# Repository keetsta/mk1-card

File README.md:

# mk1-card

hardware for mk-1, a pcb business card: an RP2350 with a 16 × 9 LED matrix, a light sensor, one button and USB-C. this repository holds the schematic, the board, the fabrication files and the scripts that generate them. the firmware lives in a separate repository.

## board

- 85.6 × 54 mm (bank card size), 4 layers, 1.0 mm, ENIG, white mask, black silkscreen
- RP2350A with the crystal and 16 MB flash of the Raspberry Pi minimal design R4. the core runs from a 1.1 V LDO instead of the on-chip switching regulator
- IS31FL3731 driving 144 red 0603 LEDs from VBUS
- TEMT6200 light sensor on ADC0 with a switchable load, AT24C02 EEPROM, USB-C with ESD protection, SWD pads on the back
- one button, wired as BOOTSEL: hold it while plugging in the cable to get the UF2 drive
- every chip sits on the back, so assembly is double-sided

pins and parts: `tools/design.py`. BOM with prices (in Russian): `bom.md`.

## build

the KiCad files are generated: change `tools/design.py` or the scripts in `tools/`, never the board or the schematic by hand. the scripts expect Windows with KiCad 9 in `C:\Program Files\KiCad\9.0` and Python 3 with `fontTools` and `openpyxl`.

```
python tools/make_fplib.py
python tools/gen_sch.py
python tools/make_text.py "tools/fonts/InterTight[wght].ttf"
"C:\Program Files\KiCad\9.0\bin\python.exe" tools/build_pcb.py
python tools/make_fab.py
python tools/make_bom.py
```

`build_pcb.py` places, routes and pours the board in about a minute. the build is deterministic: the same input gives the same board byte for byte. ERC (`kicad-cli sch erc`) and DRC (`kicad-cli pcb drc --schematic-parity`) both report 0 errors.

## ordering

JLCPCB: upload `fab/card-gerbers.zip`, `fab/card-bom.csv` and `fab/card-cpl.csv`. parts go on both sides, which means Standard PCBA with 5 mm rails on the long edges: snap them off and sand the edge. turn on parts placement confirmation and check the LED cathodes, the light sensor and pin 1 of U1..U8 in the preview.

`fab/card-cpl.csv` is written in JLC's footprint orientations. any other assembler gets `fab/card-cpl-kicad.csv` and the assembly drawings `fab/card-assembly-top.pdf` and `fab/card-assembly-bottom.pdf`.

## license

MIT, see `LICENSE`. the RP2350 core is adapted from the Raspberry Pi RP2350A minimal design (MIT, `tools/ref/LICENSE-RPi-minimal.txt`). Inter Tight is under the SIL Open Font License (`tools/fonts/OFL-InterTight.txt`).

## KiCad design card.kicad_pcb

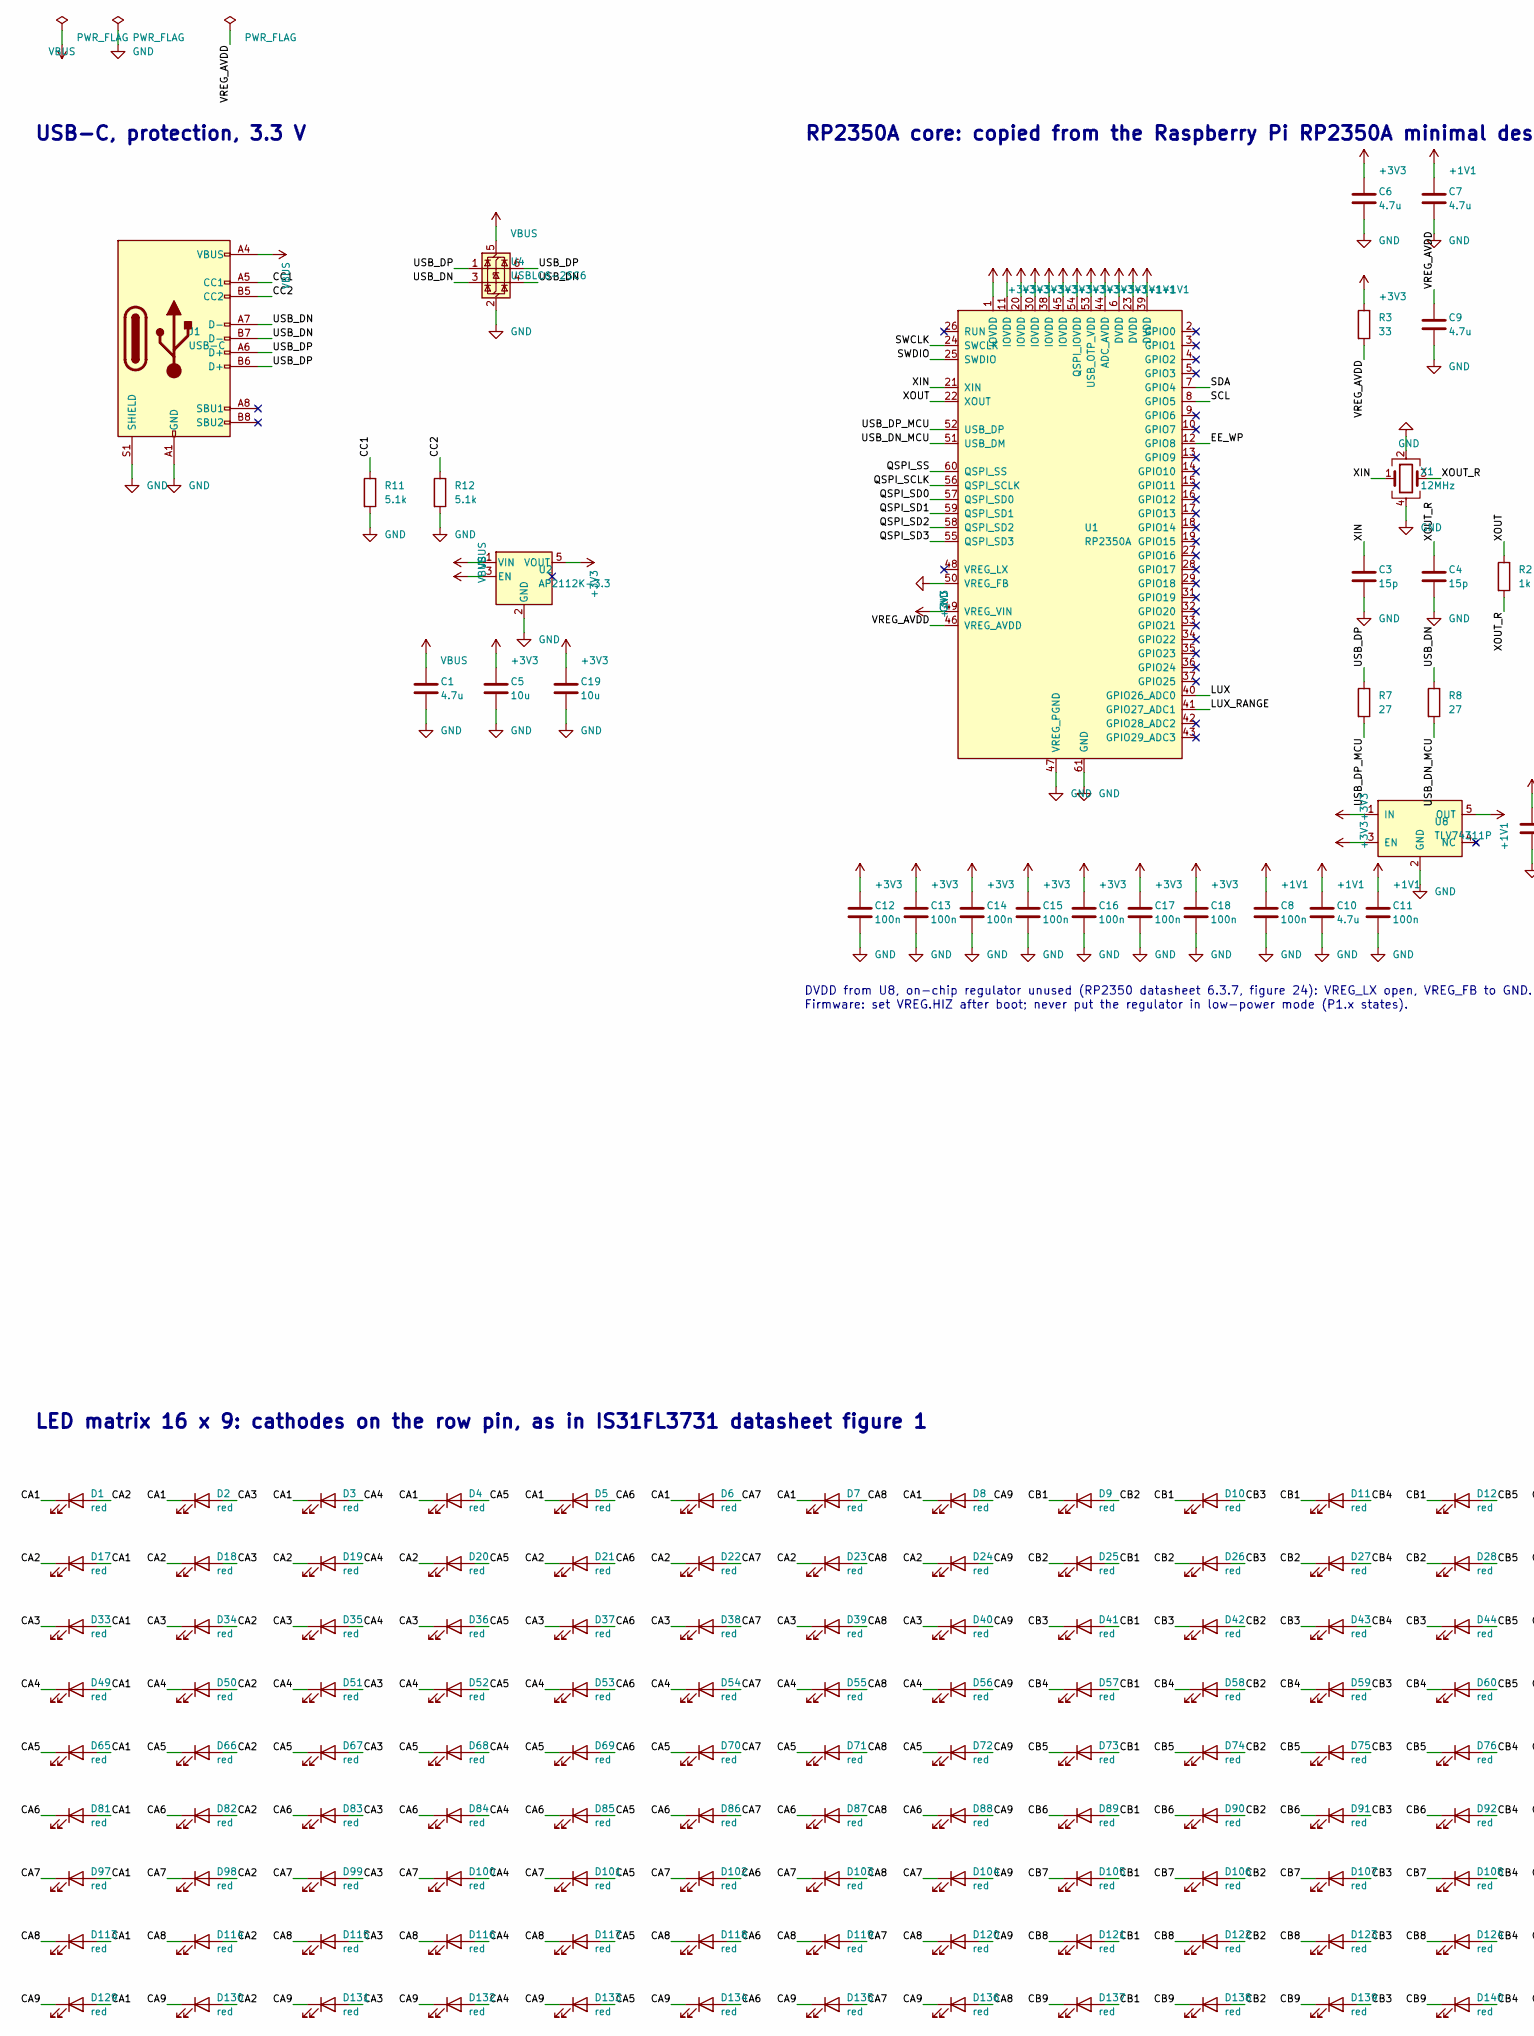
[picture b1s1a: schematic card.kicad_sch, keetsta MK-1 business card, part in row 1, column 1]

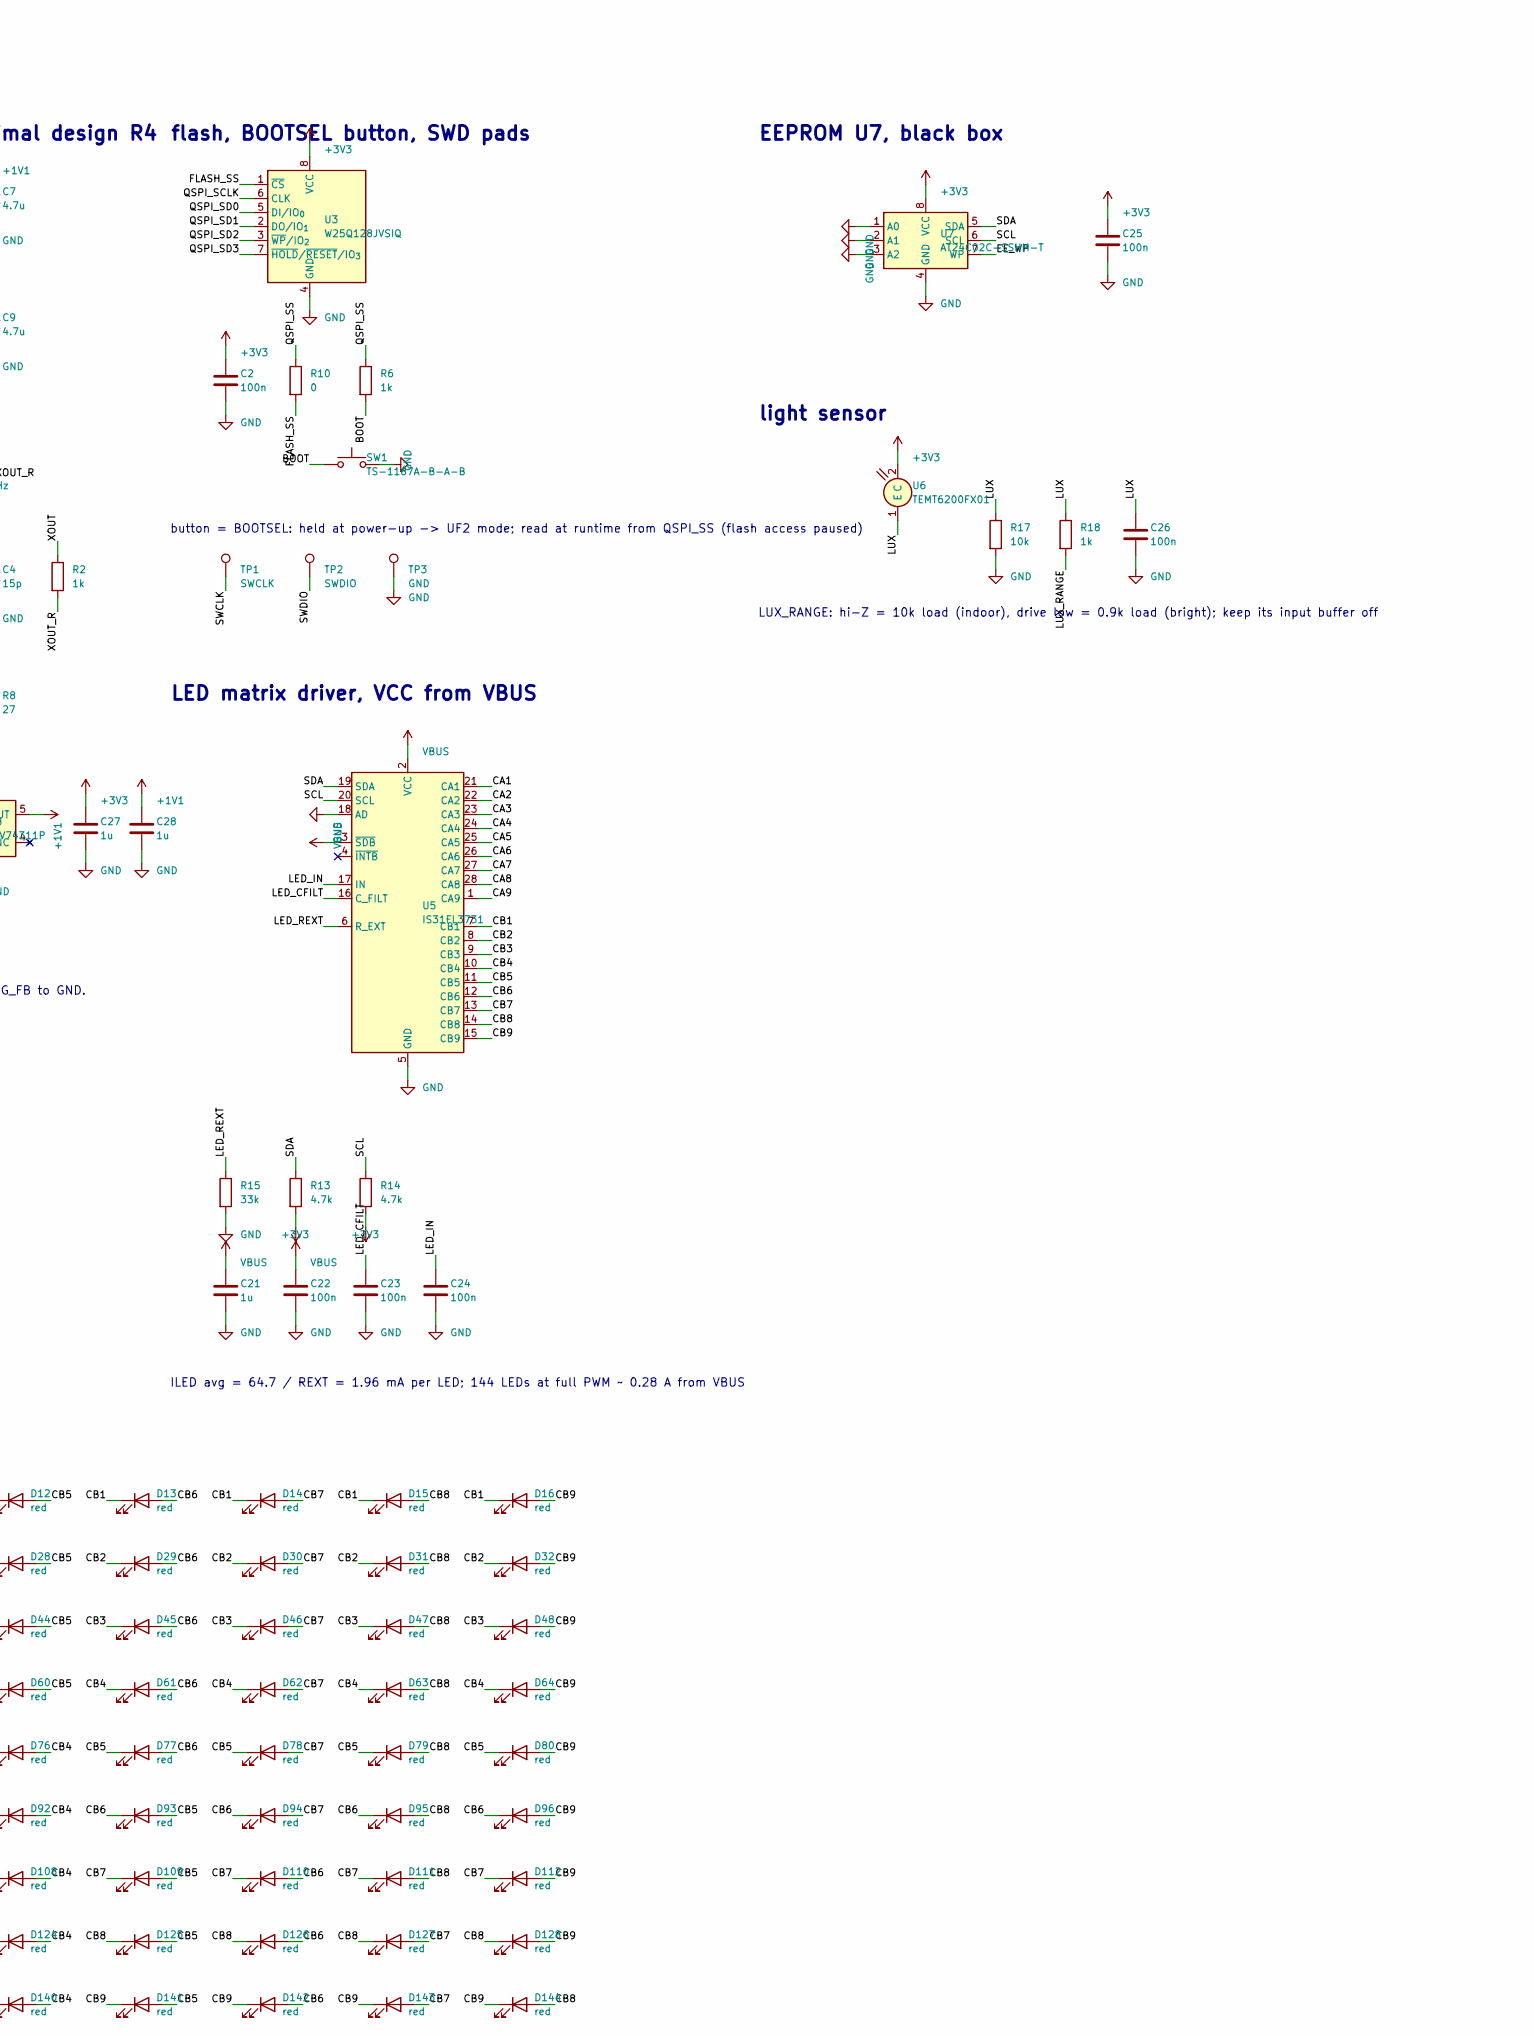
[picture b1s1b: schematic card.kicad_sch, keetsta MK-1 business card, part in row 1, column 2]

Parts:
C1: 4.7u; C_0603_1608Metric; LCSC C19666
C2, C8, C11, C12, C13, C14, C15, C16, C17, C18: 100n; RPi_capc1005x50; LCSC C1525
C3, C4: 15p; RPi_capc1005x50; LCSC C1548
C5, C19: 10u; C_0805_2012Metric; LCSC C15850
C6, C7: 4.7u; RPi_capc1005x50_wide; LCSC C23733
C9, C10: 4.7u; RPi_capc1005x50; LCSC C23733
C21, C27, C28: 1u; C_0402_1005Metric; LCSC C52923
C22, C23, C24, C25, C26: 100n; C_0402_1005Metric; LCSC C1525
D1, D2, D3, D4, D5, D6, D7, D8, D9, D10, D11, D12, D13, D14, D15, D16, D17, D18, D19, D20, D21, D22, D23, D24, D25, D26, D27, D28, D29, D30, D31, D32, D33, D34, D35, D36, D37, D38, D39, D40, D41, D42, D43, D44, D45, D46, D47, D48, D49, D50, D51, D52, D53, D54, D55, D56, D57, D58, D59, D60, D61, D62, D63, D64, D65, D66, D67, D68, D69, D70, D71, D72, D73, D74, D75, D76, D77, D78, D79, D80, D81, D82, D83, D84, D85, D86, D87, D88, D89, D90, D91, D92, D93, D94, D95, D96, D97, D98, D99, D100, D101, D102, D103, D104, D105, D106, D107, D108, D109, D110, D111, D112, D113, D114, D115, D116, D117, D118, D119, D120, D121, D122, D123, D124, D125, D126, D127, D128, D129, D130, D131, D132, D133, D134, D135, D136, D137, D138, D139, D140, D141, D142, D143, D144: red; LED_0603_KT; LCSC C2286
J1: USB-C; USB_C_Receptacle_HRO_TYPE-C-31-M-12; LCSC C165948
R2, R6: 1k; RPi_resc1005x35; LCSC C11702
R3: 33; RPi_resc1005x35; LCSC C25105
R7, R8: 27; RPi_resc1005x35; LCSC C25100
R10: 0; RPi_resc1005x35; LCSC C17168
R11, R12: 5.1k; R_0402_1005Metric; LCSC C25905
R13, R14: 4.7k; R_0402_1005Metric; LCSC C25900
R15: 33k; R_0402_1005Metric; LCSC C25779
R17: 10k; R_0402_1005Metric; LCSC C25744
R18: 1k; R_0402_1005Metric; LCSC C11702
SW1: TS-1187A-B-A-B; SW_Push_1P1T_XKB_TS-1187A; LCSC C318884
TP1: SWCLK; TestPoint_Pad_D1.0mm
TP2: SWDIO; TestPoint_Pad_D1.0mm
TP3: GND; TestPoint_Pad_D1.0mm
U1: RP2350A; RPi_rp2350a_vias; LCSC C42411118
U2: AP2112K-3.3; SOT-23-5; LCSC C51118
U3: W25Q128JVSIQ; RPi_soic127p790x195-8; LCSC C97521
U4: USBLC6-2SC6; SOT-23-6; LCSC C7519
U5: IS31FL3731; QFN-28-1EP_4x4mm_P0.4mm_EP2.4x2.4mm_ThermalVias; LCSC C191206
U6: TEMT6200FX01; LCSC C143695
U7: AT24C02C-SSHM-T; SOIC-8_3.9x4.9mm_P1.27mm; LCSC C6203
U8: TLV74311P; SOT-23-5; LCSC C485147
X1: 12MHz; RPi_xtalcc320x250x80-4; LCSC C20625731

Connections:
+1V1: C7.1, C8.1, C10.1, C11.1, C28.1, U1.6 (DVDD), U1.23 (DVDD), U1.39 (DVDD), U8.5 (OUT)
+3V3: C2.1, C5.1, C6.1, C12.1, C13.1, C14.1, C15.1, C16.1, C17.1, C18.1, C19.1, C25.1, C27.1, R3.1, R13.2, R14.2, U1.1 (IOVDD), U1.11 (IOVDD), U1.20 (IOVDD), U1.30 (IOVDD), U1.38 (IOVDD), U1.44 (ADC_AVDD), U1.45 (IOVDD), U1.49 (VREG_VIN), U1.53 (USB_OTP_VDD), U1.54 (QSPI_IOVDD), U2.5 (VOUT), U3.8 (VCC), U6.2 (C), U7.8 (VCC), U8.1 (IN), U8.3 (EN)
/BOOT: R6.2, SW1.1
/CA1: D1.1 (K), D2.1 (K), D3.1 (K), D4.1 (K), D5.1 (K), D6.1 (K), D7.1 (K), D8.1 (K), D17.2 (A), D33.2 (A), D49.2 (A), D65.2 (A), D81.2 (A), D97.2 (A), D113.2 (A), D129.2 (A), U5.21 (CA1)
/CA2: D1.2 (A), D17.1 (K), D18.1 (K), D19.1 (K), D20.1 (K), D21.1 (K), D22.1 (K), D23.1 (K), D24.1 (K), D34.2 (A), D50.2 (A), D66.2 (A), D82.2 (A), D98.2 (A), D114.2 (A), D130.2 (A), U5.22 (CA2)
/CA3: D2.2 (A), D18.2 (A), D33.1 (K), D34.1 (K), D35.1 (K), D36.1 (K), D37.1 (K), D38.1 (K), D39.1 (K), D40.1 (K), D51.2 (A), D67.2 (A), D83.2 (A), D99.2 (A), D115.2 (A), D131.2 (A), U5.23 (CA3)
/CA4: D3.2 (A), D19.2 (A), D35.2 (A), D49.1 (K), D50.1 (K), D51.1 (K), D52.1 (K), D53.1 (K), D54.1 (K), D55.1 (K), D56.1 (K), D68.2 (A), D84.2 (A), D100.2 (A), D116.2 (A), D132.2 (A), U5.24 (CA4)
/CA5: D4.2 (A), D20.2 (A), D36.2 (A), D52.2 (A), D65.1 (K), D66.1 (K), D67.1 (K), D68.1 (K), D69.1 (K), D70.1 (K), D71.1 (K), D72.1 (K), D85.2 (A), D101.2 (A), D117.2 (A), D133.2 (A), U5.25 (CA5)
/CA6: D5.2 (A), D21.2 (A), D37.2 (A), D53.2 (A), D69.2 (A), D81.1 (K), D82.1 (K), D83.1 (K), D84.1 (K), D85.1 (K), D86.1 (K), D87.1 (K), D88.1 (K), D102.2 (A), D118.2 (A), D134.2 (A), U5.26 (CA6)
/CA7: D6.2 (A), D22.2 (A), D38.2 (A), D54.2 (A), D70.2 (A), D86.2 (A), D97.1 (K), D98.1 (K), D99.1 (K), D100.1 (K), D101.1 (K), D102.1 (K), D103.1 (K), D104.1 (K), D119.2 (A), D135.2 (A), U5.27 (CA7)
/CA8: D7.2 (A), D23.2 (A), D39.2 (A), D55.2 (A), D71.2 (A), D87.2 (A), D103.2 (A), D113.1 (K), D114.1 (K), D115.1 (K), D116.1 (K), D117.1 (K), D118.1 (K), D119.1 (K), D120.1 (K), D136.2 (A), U5.28 (CA8)
/CA9: D8.2 (A), D24.2 (A), D40.2 (A), D56.2 (A), D72.2 (A), D88.2 (A), D104.2 (A), D120.2 (A), D129.1 (K), D130.1 (K), D131.1 (K), D132.1 (K), D133.1 (K), D134.1 (K), D135.1 (K), D136.1 (K), U5.1 (CA9)
/CB1: D9.1 (K), D10.1 (K), D11.1 (K), D12.1 (K), D13.1 (K), D14.1 (K), D15.1 (K), D16.1 (K), D25.2 (A), D41.2 (A), D57.2 (A), D73.2 (A), D89.2 (A), D105.2 (A), D121.2 (A), D137.2 (A), U5.7 (CB1)
/CB2: D9.2 (A), D25.1 (K), D26.1 (K), D27.1 (K), D28.1 (K), D29.1 (K), D30.1 (K), D31.1 (K), D32.1 (K), D42.2 (A), D58.2 (A), D74.2 (A), D90.2 (A), D106.2 (A), D122.2 (A), D138.2 (A), U5.8 (CB2)
/CB3: D10.2 (A), D26.2 (A), D41.1 (K), D42.1 (K), D43.1 (K), D44.1 (K), D45.1 (K), D46.1 (K), D47.1 (K), D48.1 (K), D59.2 (A), D75.2 (A), D91.2 (A), D107.2 (A), D123.2 (A), D139.2 (A), U5.9 (CB3)
/CB4: D11.2 (A), D27.2 (A), D43.2 (A), D57.1 (K), D58.1 (K), D59.1 (K), D60.1 (K), D61.1 (K), D62.1 (K), D63.1 (K), D64.1 (K), D76.2 (A), D92.2 (A), D108.2 (A), D124.2 (A), D140.2 (A), U5.10 (CB4)
/CB5: D12.2 (A), D28.2 (A), D44.2 (A), D60.2 (A), D73.1 (K), D74.1 (K), D75.1 (K), D76.1 (K), D77.1 (K), D78.1 (K), D79.1 (K), D80.1 (K), D93.2 (A), D109.2 (A), D125.2 (A), D141.2 (A), U5.11 (CB5)
/CB6: D13.2 (A), D29.2 (A), D45.2 (A), D61.2 (A), D77.2 (A), D89.1 (K), D90.1 (K), D91.1 (K), D92.1 (K), D93.1 (K), D94.1 (K), D95.1 (K), D96.1 (K), D110.2 (A), D126.2 (A), D142.2 (A), U5.12 (CB6)
/CB7: D14.2 (A), D30.2 (A), D46.2 (A), D62.2 (A), D78.2 (A), D94.2 (A), D105.1 (K), D106.1 (K), D107.1 (K), D108.1 (K), D109.1 (K), D110.1 (K), D111.1 (K), D112.1 (K), D127.2 (A), D143.2 (A), U5.13 (CB7)
/CB8: D15.2 (A), D31.2 (A), D47.2 (A), D63.2 (A), D79.2 (A), D95.2 (A), D111.2 (A), D121.1 (K), D122.1 (K), D123.1 (K), D124.1 (K), D125.1 (K), D126.1 (K), D127.1 (K), D128.1 (K), D144.2 (A), U5.14 (CB8)
/CB9: D16.2 (A), D32.2 (A), D48.2 (A), D64.2 (A), D80.2 (A), D96.2 (A), D112.2 (A), D128.2 (A), D137.1 (K), D138.1 (K), D139.1 (K), D140.1 (K), D141.1 (K), D142.1 (K), D143.1 (K), D144.1 (K), U5.15 (CB9)
/CC1: J1.A5 (CC1), R11.1
/CC2: J1.B5 (CC2), R12.1
/EE_WP: U1.12 (GPIO8), U7.7 (WP)
/FLASH_SS: R10.2, U3.1 (~CS)
/LED_CFILT: C23.1, U5.16 (C_FILT)
/LED_IN: C24.1, U5.17 (IN)
/LED_REXT: R15.1, U5.6 (R_EXT)
/LUX: C26.1, R17.1, R18.1, U1.40 (GPIO26_ADC0), U6.1 (E)
/LUX_RANGE: R18.2, U1.41 (GPIO27_ADC1)
/QSPI_SCLK: U1.56 (QSPI_SCLK), U3.6 (CLK)
/QSPI_SD0: U1.57 (QSPI_SD0), U3.5 (DI/IO_{0})
/QSPI_SD1: U1.59 (QSPI_SD1), U3.2 (DO/IO_{1})
/QSPI_SD2: U1.58 (QSPI_SD2), U3.3 (~WP/IO_{2})
/QSPI_SD3: U1.55 (QSPI_SD3), U3.7 (~HOLD/~RESET/IO_{3})
/QSPI_SS: R6.1, R10.1, U1.60 (QSPI_SS)
/SCL: R14.1, U1.8 (GPIO5), U5.20 (SCL), U7.6 (SCL)
/SDA: R13.1, U1.7 (GPIO4), U5.19 (SDA), U7.5 (SDA)
/SWCLK: TP1.1, U1.24 (SWCLK)
/SWDIO: TP2.1, U1.25 (SWDIO)
/USB_DN: J1.A7 (D-), J1.B7 (D-), R8.1, U4.3 (I/O2), U4.4 (I/O2)
/USB_DN_MCU: R8.2, U1.51 (USB_DM)
/USB_DP: J1.A6 (D+), J1.B6 (D+), R7.1, U4.1 (I/O1), U4.6 (I/O1)
/USB_DP_MCU: R7.2, U1.52 (USB_DP)
/VREG_AVDD: C9.1, R3.2, U1.46 (VREG_AVDD)
/XIN: C3.1, U1.21 (XIN), X1.1
/XOUT: R2.1, U1.22 (XOUT)
/XOUT_R: C4.1, R2.2, X1.3
GND: C1.2, C2.2, C3.2, C4.2, C5.2, C6.2, C7.2, C8.2, C9.2, C10.2, C11.2, C12.2, C13.2, C14.2, C15.2, C16.2, C17.2, C18.2, C19.2, C21.2, C22.2, C23.2, C24.2, C25.2, C26.2, C27.2, C28.2, J1.A1 (GND), J1.A12 (GND), J1.B1 (GND), J1.B12 (GND), J1.S1 (SHIELD), R11.2, R12.2, R15.2, R17.2, SW1.2, TP3.1, U1.47 (VREG_PGND), U1.50 (VREG_FB), U1.61 (GND), U2.2 (GND), U3.4 (GND), U4.2 (GND), U5.5 (GND), U5.18 (AD), U5.29 (GND), U7.1 (A0), U7.2 (A1), U7.3 (A2), U7.4 (GND), U8.2 (GND), X1.2, X1.4
VBUS: C1.1, C21.1, C22.1, J1.A4 (VBUS), J1.A9 (VBUS), J1.B4 (VBUS), J1.B9 (VBUS), U2.1 (VIN), U2.3 (EN), U4.5 (VBUS), U5.2 (VCC), U5.3 (~SDB)

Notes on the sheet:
USB-C, protection, 3.3 V
RP2350A core: copied from the Raspberry Pi RP2350A minimal design R4
flash, BOOTSEL button, SWD pads
LED matrix driver, VCC from VBUS
EEPROM U7, black box
light sensor
LED matrix 16 x 9: cathodes on the row pin, as in IS31FL3731 datasheet figure 1
button = BOOTSEL: held at power-up -> UF2 mode; read at runtime from QSPI_SS (flash access paused)
ILED avg = 64.7 / REXT = 1.96 mA per LED; 144 LEDs at full PWM ~ 0.28 A from VBUS
LUX_RANGE: hi-Z = 10k load (indoor), drive low = 0.9k load (bright); keep its input buffer off
DVDD from U8, on-chip regulator unused (RP2350 datasheet 6.3.7, figure 24): VREG_LX open, VREG_FB to GND.
Firmware: set VREG.HIZ after boot; never put the regulator in low-power mode (P1.x states).

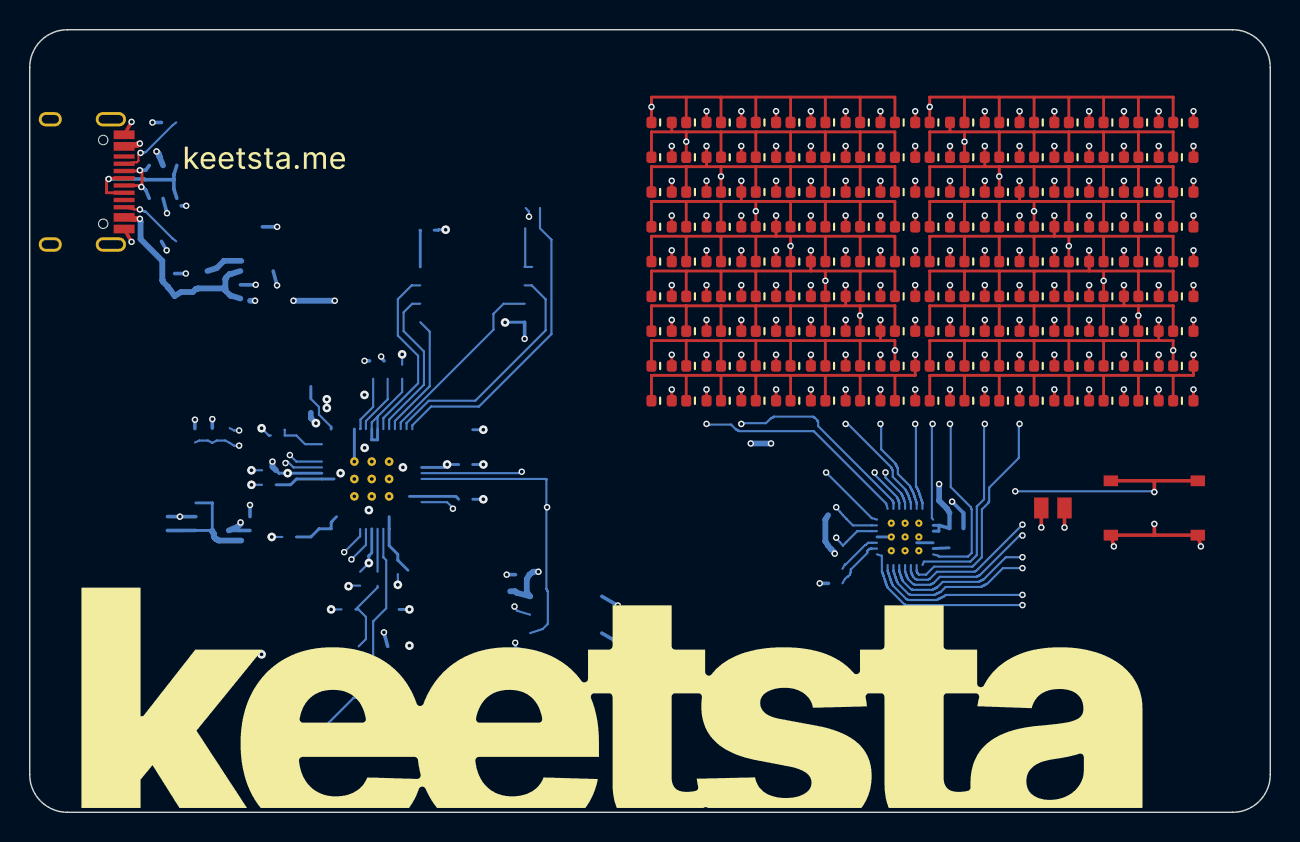
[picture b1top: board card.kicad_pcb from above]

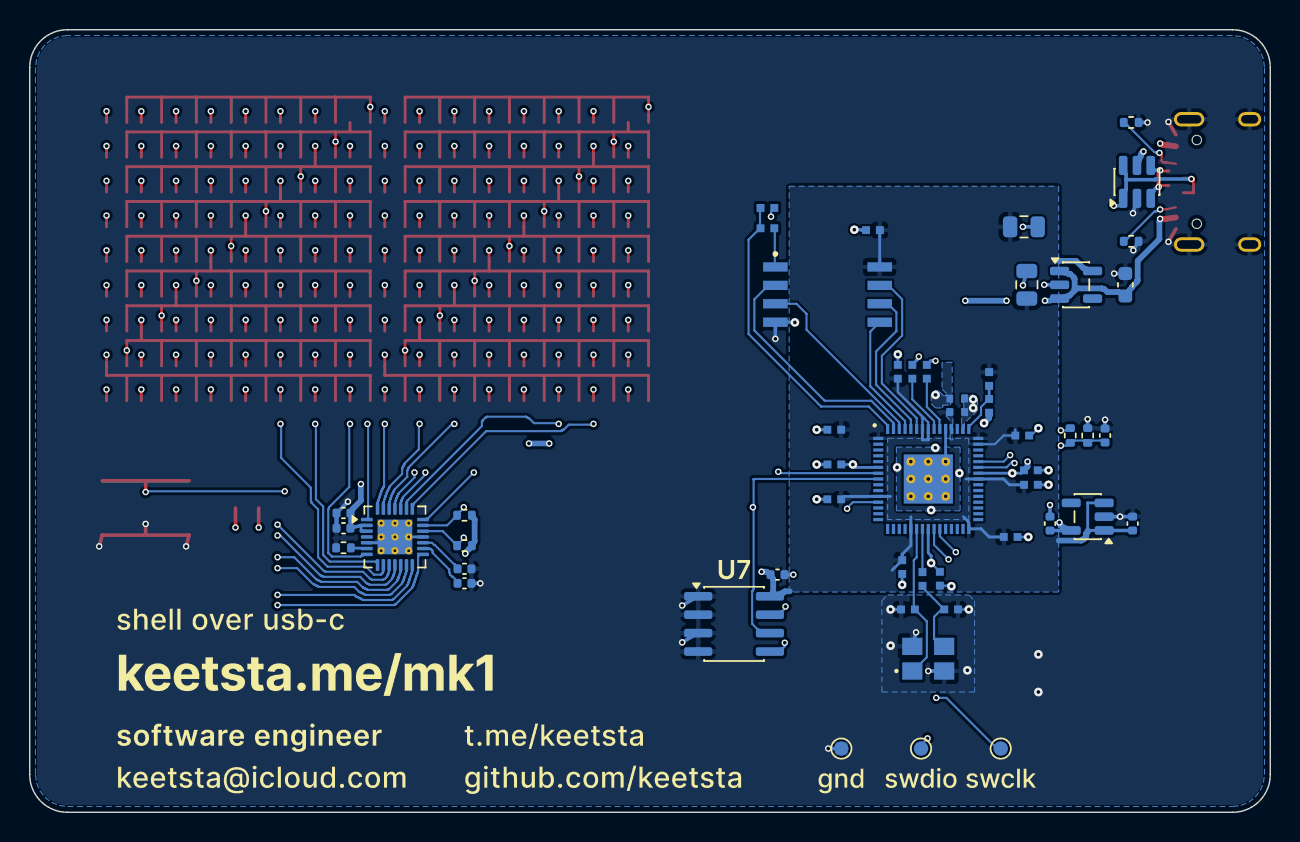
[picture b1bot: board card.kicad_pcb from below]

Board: 4 copper layers, 85.6 x 54.0 mm, 198 parts (51 on the bottom side), 50 nets.

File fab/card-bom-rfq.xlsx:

MK-1 business card: bill of materials
Project |  | MK-1 business card (keetsta)
PCB |  | 85.6 x 54 mm, 4 layers, 1.0 mm, ENIG, white solder mask, black silkscreen
Panel |  | single board with 5 mm rails on both long sides (85.6 x 64 mm)
Assembly |  | double-sided SMT; top: LEDs, USB-C, button, light sensor; bottom: everything el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
Not placed |  | TP1, TP2, TP3 are bare test pads, no parts
Request |  | please confirm stock, lead time and price per line; offer substitutes only wher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
Boards |  | 10
# | Designators | Qty / board | Qty total | Side | Description | Manufacturer | MPN | LCSC # | Substitute allowed | Notes
1 | C1 | 1 | 10 | Bottom | MLCC 4.7 uF 16 V X5R 10%, 0603 | Samsung | CL10A475KO8NNNC | C19666 | Yes: same value, size, tolerance, voltage and dielectric or better
2 | C2, C8, C11, C12, C13, C14, C15, C16, C17, C18, C22, C23, C24, C25, C26 | 15 | 150 | Bottom | MLCC 100 nF 16 V X7R 10%, 0402 | Samsung | CL05B104KO5NNNC | C1525 | Yes: same value, size, tolerance, voltage and dielectric or better
3 | C3, C4 | 2 | 20 | Bottom | MLCC 15 pF 50 V C0G 5%, 0402 | Fenghua (FH) | 0402CG150J500NT | C1548 | Yes: same value, size, tolerance, voltage and dielectric or better
4 | C5, C19 | 2 | 20 | Bottom | MLCC 10 uF 25 V X5R 10%, 0805 | Samsung | CL21A106KAYNNNE | C15850 | Yes: same value, size, tolerance, voltage and dielectric or better
5 | C6, C7, C9, C10 | 4 | 40 | Bottom | MLCC 4.7 uF 10 V X5R 20%, 0402 | Samsung | CL05A475MP5NRNC | C23733 | Yes: same value, size, tolerance, voltage and dielectric or better
6 | C21, C27, C28 | 3 | 30 | Bottom | MLCC 1 uF 25 V X5R 10%, 0402 | Samsung | CL05A105KA5NQNC | C52923 | Yes: same value, size, tolerance, voltage and dielectric or better
7 | D1-D144 | 144 | 1440 | Top | LED red 620 nm, water clear, 0603 | Hubei KENTO | KT-0603R | C2286 | No: all 144 from one lot, they form the visible display
8 | J1 | 1 | 10 | Top | USB Type-C receptacle 16 pin, SMD + 4 shell pins | Korean Hroparts (HRO) | TYPE-C-31-M-12 | C165948 | No
9 | R2, R6, R18 | 3 | 30 | Bottom | Resistor 1 kohm 1% 1/16 W, 0402 | UNI-ROYAL | 0402WGF1001TCE | C11702 | Yes: same value, size, tolerance, voltage and dielectric or better
10 | R3 | 1 | 10 | Bottom | Resistor 33 ohm 1% 1/16 W, 0402 | UNI-ROYAL | 0402WGF330JTCE | C25105 | Yes: same value, size, tolerance, voltage and dielectric or better
11 | R7, R8 | 2 | 20 | Bottom | Resistor 27 ohm 1% 1/16 W, 0402 | UNI-ROYAL | 0402WGF270JTCE | C25100 | Yes: same value, size, tolerance, voltage and dielectric or better | any 27 ohm 0402 is fine, no need for a full reel
12 | R10 | 1 | 10 | Bottom | Resistor 0 ohm, 0402 | UNI-ROYAL | 0402WGF0000TCE | C17168 | Yes: same value, size, tolerance, voltage and dielectric or better
13 | R11, R12 | 2 | 20 | Bottom | Resistor 5.1 kohm 1% 1/16 W, 0402 | UNI-ROYAL | 0402WGF5101TCE | C25905 | Yes: same value, size, tolerance, voltage and dielectric or better
14 | R13, R14 | 2 | 20 | Bottom | Resistor 4.7 kohm 1% 1/16 W, 0402 | UNI-ROYAL | 0402WGF4701TCE | C25900 | Yes: same value, size, tolerance, voltage and dielectric or better
15 | R15 | 1 | 10 | Bottom | Resistor 33 kohm 1% 1/16 W, 0402 | UNI-ROYAL | 0402WGF3302TCE | C25779 | Yes: same value, size, tolerance, voltage and dielectric or better
16 | R17 | 1 | 10 | Bottom | Resistor 10 kohm 1% 1/16 W, 0402 | UNI-ROYAL | 0402WGF1002TCE | C25744 | Yes: same value, size, tolerance, voltage and dielectric or better
17 | SW1 | 1 | 10 | Top | Tactile switch SPST, SMD 5.1x5.1 | XKB Connection | TS-1187A-B-A-B | C318884 | Ask first: same footprint
18 | U1 | 1 | 10 | Bottom | MCU, dual Cortex-M33/RISC-V, QFN-60 7x7 | Raspberry Pi | RP2350A | C42411118 | No
19 | U2 | 1 | 10 | Bottom | LDO 3.3 V 600 mA with enable, SOT-23-5 | Diodes Inc. | AP2112K-3.3TRG1 | C51118 | Ask first: same pinout only
20 | U3 | 1 | 10 | Bottom | QSPI NOR flash 128 Mbit, SOIC-8 208 mil | Winbond | W25Q128JVSIQ | C97521 | No
21 | U4 | 1 | 10 | Bottom | USB ESD protection, SOT-23-6 | STMicroelectronics | USBLC6-2SC6 | C7519 | Ask first: same pinout only
22 | U5 | 1 | 10 | Bottom | LED matrix driver 144 LEDs, I2C, QFN-28 4x4 | Lumissil (ISSI) | IS31FL3731-QFLS2-TR | C191206 | No
23 | U6 | 1 | 10 | Top | Ambient light sensor, phototransistor, 0805 | Vishay | TEMT6200FX01 | C143695 | No
24 | U7 | 1 | 10 | Bottom | EEPROM 2 Kbit I2C with WP pin, SOIC-8 | Microchip | AT24C02C-SSHM-T | C6203 | Yes: any 24C02, SOIC-8, same pinout
25 | U8 | 1 | 10 | Bottom | LDO 1.1 V 300 mA with enable, SOT-23-5 | Texas Instruments | TLV74311PDBVR | C485147 | Ask first: fixed 1.1 V, >= 200 mA, same pinout (1 IN, 2 GND, 3 EN, 4 NC, 5 OUT)
26 | X1 | 1 | 10 | Bottom | Crystal 12 MHz, 10 pF load, 3225 | Abracon | ABM8-272-T3 | C20625731 | No: Raspberry Pi recommends this exact part
 | Total | 195 | 1950 |  | 26 unique parts

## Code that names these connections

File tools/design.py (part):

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}

RP2350A_PINS = {
    1: 'IOVDD', 2: 'GPIO0', 3: 'GPIO1', 4: 'GPIO2', 5: 'GPIO3', 6: 'DVDD', 7: 'GPIO4', 8: 'GPIO5',
    9: 'GPIO6', 10: 'GPIO7', 11: 'IOVDD', 12: 'GPIO8', 13: 'GPIO9', 14: 'GPIO10', 15: 'GPIO11',
    16: 'GPIO12', 17: 'GPIO13', 18: 'GPIO14', 19: 'GPIO15', 20: 'IOVDD', 21: 'XIN', 22: 'XOUT',
    23: 'DVDD', 24: 'SWCLK', 25: 'SWDIO', 26: 'RUN', 27: 'GPIO16', 28: 'GPIO17', 29: 'GPIO18',
    30: 'IOVDD', 31: 'GPIO19', 32: 'GPIO20', 33: 'GPIO21', 34: 'GPIO22', 35: 'GPIO23', 36: 'GPIO24',
    37: 'GPIO25', 38: 'IOVDD', 39: 'DVDD', 40: 'GPIO26_ADC0', 41: 'GPIO27_ADC1', 42: 'GPIO28_ADC2',
    43: 'GPIO29_ADC3', 44: 'ADC_AVDD', 45: 'IOVDD', 46: 'VREG_AVDD', 47: 'VREG_PGND', 48: 'VREG_LX',
    49: 'VREG_VIN', 50: 'VREG_FB', 51: 'USB_DM', 52: 'USB_DP', 53: 'USB_OTP_VDD', 54: 'QSPI_IOVDD',
    55: 'QSPI_SD3', 56: 'QSPI_SCLK', 57: 'QSPI_SD0', 58: 'QSPI_SD2', 59: 'QSPI_SD1', 60: 'QSPI_SS',
    61: 'GND',
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
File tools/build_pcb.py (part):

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            '/QSPI_SCLK': 'QSPI_SCLK', '/QSPI_SD0': 'QSPI_SD0', '/QSPI_SD1': 'QSPI_SD1', '/QSPI_SD2': 'QSPI_SD2',
            '/QSPI_SD3': 'QSPI_SD3',
            # fan-outs of the pins we use: copied up to the edge of the core, the router carries them on
            '/GPIO4': 'SDA', '/GPIO5': 'SCL', '/GPIO8': 'EE_WP', '/GPIO26_ADC0': 'LUX',
            '/GPIO27_ADC1': 'LUX_RANGE'}
ESCAPES = {'SDA', 'SCL', 'EE_WP', 'LUX', 'LUX_RANGE'}
# nets the reference layout connects completely inside the core (+3V3, GND and +1V1 from U8 reach in from outside)
CORE_NETS = {'VREG_AVDD', 'XIN', 'XOUT', 'XOUT_R', 'USB_DP_MCU', 'USB_DN_MCU', 'QSPI_SS',
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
